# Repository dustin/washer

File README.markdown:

This is the code that supports my [laundry][blog] project.

[blog]: http://dustin.sallings.org/2012/09/16/wash.html

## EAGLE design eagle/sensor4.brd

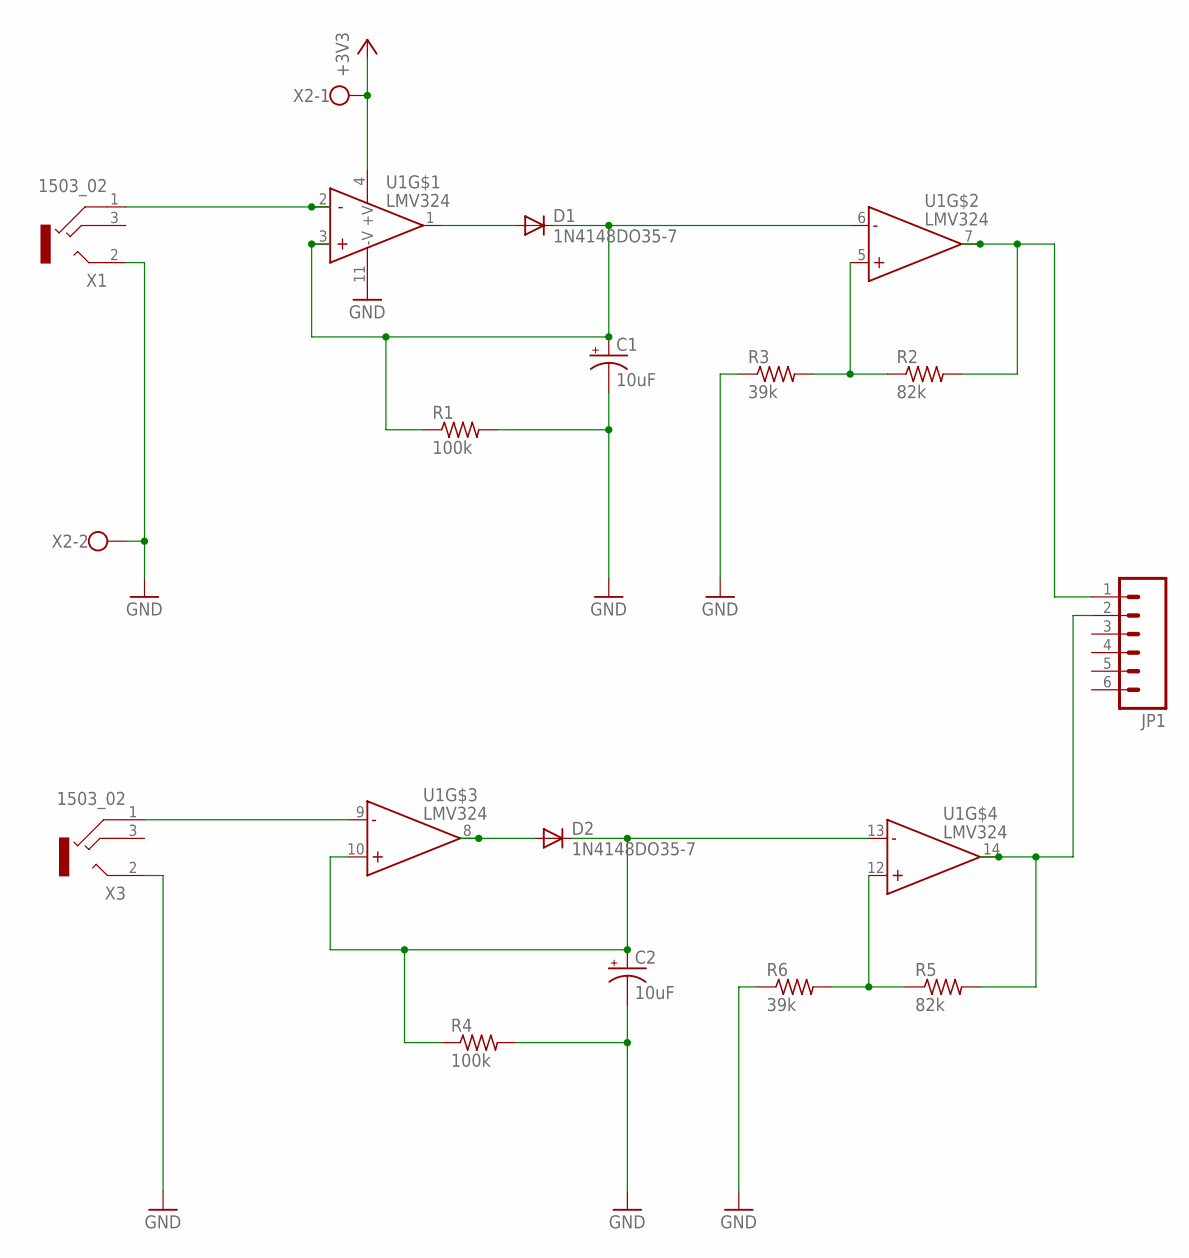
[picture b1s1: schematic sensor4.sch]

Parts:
C1, C2: 10uF; E2,5-5
D1, D2: 1N4148DO35-7; DO35-7
JP1: M06SIP; 1X06
R1, R4: 100k; 0207/10
R2, R5: 82k; 0207/10
R3, R6: 39k; 0207/10
U1: LMV324; SO014
X1, X3: 1503_02
X2: W237-102

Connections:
+3V3: U1.4 (+V), X2.1
GND: C1.-, C2.-, R1.2, R3.1, R4.2, R6.1, U1.11 (-V), X1.2, X2.2, X3.2
unnamed: D1.A, U1.1 (OUT)
unnamed: C1.+, D1.C, R1.1, U1.3 (+IN), U1.6 (-IN)
unnamed: D2.A, U1.8 (OUT)
unnamed: C2.+, D2.C, R4.1, U1.10 (+IN), U1.13 (-IN)
unnamed: R2.1, R3.2, U1.5 (+IN)
unnamed: U1.2 (-IN), X1.1
unnamed: JP1.1, R2.2, U1.7 (OUT)
unnamed: R5.1, R6.2, U1.12 (+IN)
unnamed: U1.9 (-IN), X3.1
unnamed: JP1.2, R5.2, U1.14 (OUT)

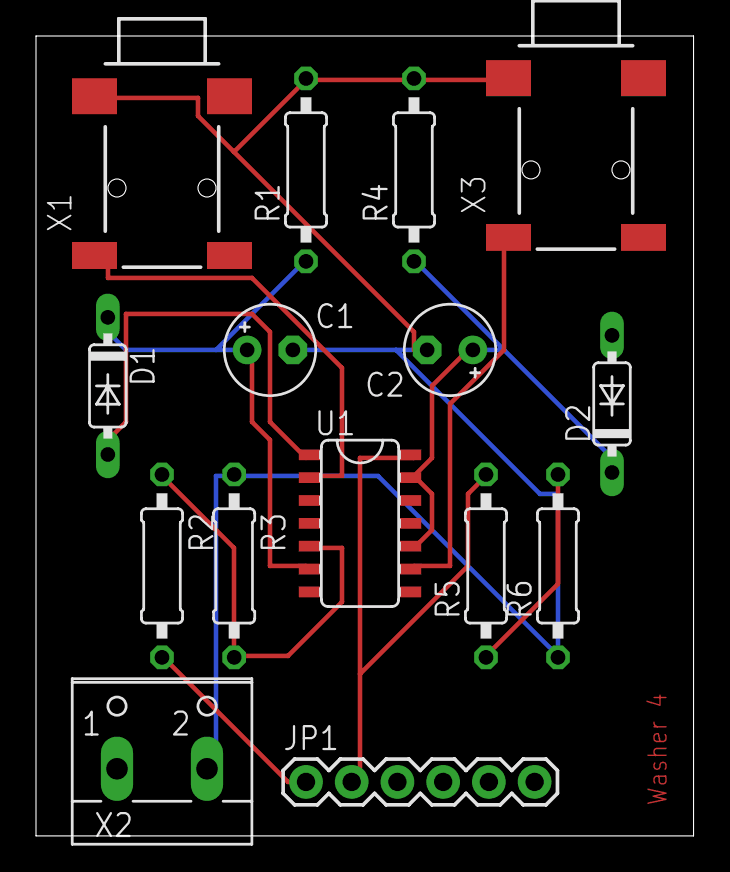
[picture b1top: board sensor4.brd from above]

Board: 2 copper layers, 36.5 x 44.4 mm, 15 parts (0 on the bottom side), 12 nets.

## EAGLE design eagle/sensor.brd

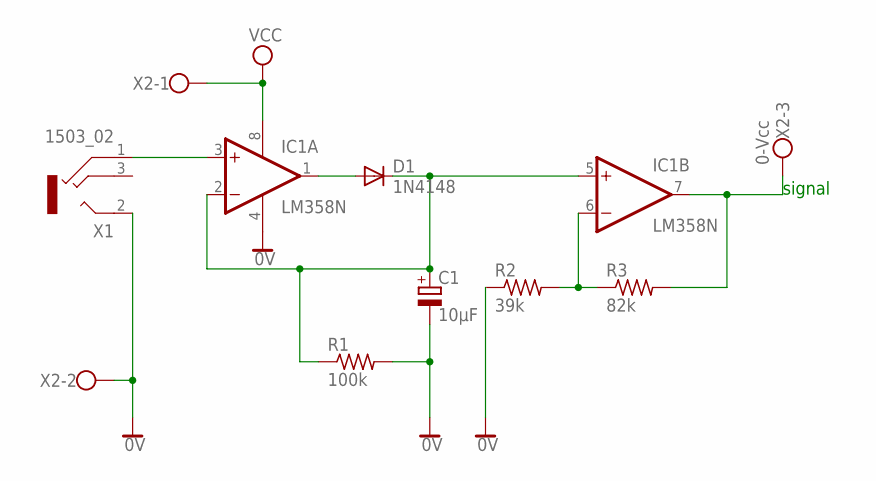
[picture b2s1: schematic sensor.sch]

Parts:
C1: 10µF; E2,5-6E
D1: 1N4148; DO35-10
IC1: LM358N; DIL08
R1: 100k; 0207/10
R2: 39k; 0207/10
R3: 82k; 0207/10
X1: 1503_02
X2: 0-Vcc; W237-103

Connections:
0V: C1.-, IC1.4 (V-), R1.2, R2.1, X1.2, X2.2
unnamed: C1.+, D1.C, IC1.2 (-IN), IC1.5 (+IN), R1.1
unnamed: IC1.6 (-IN), R2.2, R3.1
unnamed: D1.A, IC1.1 (OUT)
unnamed: IC1.7 (OUT), R3.2, X2.3
unnamed: IC1.3 (+IN), X1.1
VCC: IC1.8 (V+), X2.1

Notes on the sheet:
signal

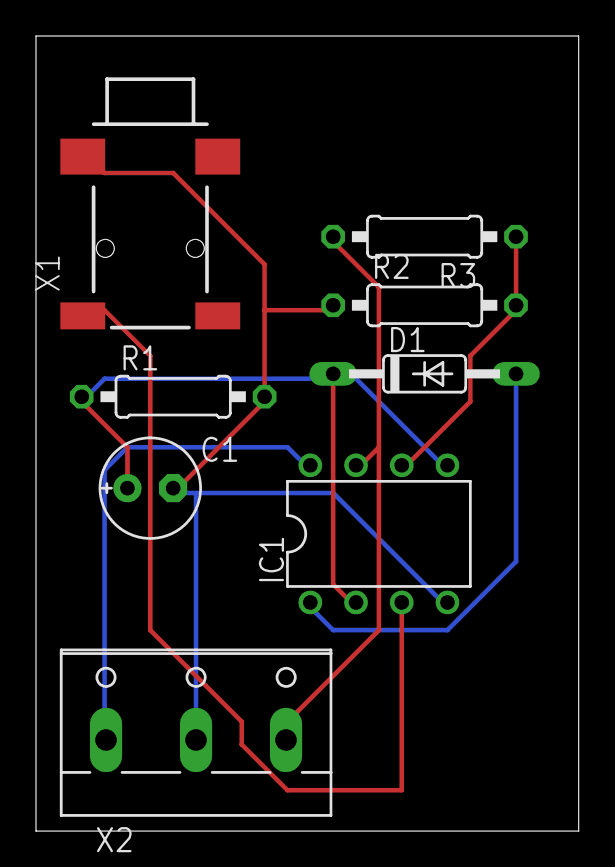
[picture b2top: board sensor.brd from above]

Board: 2 copper layers, 30.1 x 44.2 mm, 8 parts (0 on the bottom side), 7 nets.

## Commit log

2011-12-25 Semi-working version tested in garage.
2011-12-26 Report time since last state change.
2011-12-26 Conveniently clean date formatting.
2011-12-26 Indicate state on/off
2011-12-26 Newer lighter home protocol.
2011-12-26 Removed an unused var.
2011-12-26 More protocol updates.
2011-12-26 Added a go based monitor prog.
2011-12-26 Include previous time in event state change.
2011-12-26 gofmt -- I should automate this at some point.
2011-12-26 Build and initialize the struct.
2011-12-27 Keep transmitting the high since last ACK.
2011-12-27 Static'd out the variables.
2011-12-27 Track maximum value seen since ACK.
2012-01-02 Minor refactoring.
2012-01-02 Added support for mocking a device.
2012-01-02 Added a simple web interface.
2012-01-09 Slipping in a blinking state between off/on cycle.
2012-01-09 Replace serial delays with flushes.
2012-01-09 Clean up blink state overlay.
2012-02-08 Updated for 'go build'
2012-06-22 Ignore the built monitor.
2012-06-22 RS232 API updates.
2012-06-23 Deal with empty lines from the monitor.
2012-06-23 Use custom marshaler.
2012-06-23 Don't be confusing and alias my types.
2012-06-23 Notification with a stability timer.
2012-06-23 Allow user to specify which events receive the notification.
2012-06-23 Have to actually start the notifier.
2012-06-24 Added HTML view.
    Since rendering the JSON on my phone was awful.
2012-06-24 Set CORS and content type headers for JSON.
2012-06-25 Building and deploying Arduino code on Linux now.
2012-10-20 Log to syslog.
2012-10-20 Don't duplicate the timestamps when logging to syslog.
2012-11-05 Fix notification disabling.
2013-07-29 Renamed nma
2013-07-29 Renamed rs232
2013-08-04 nma priority level update
2013-09-14 Initialize globals outside of init
2013-09-14 No need to name the tracker's state type
2013-09-15 Added a README
2013-09-16 Original eagle work.
2013-09-16 Rerouted board for two layer print.
2013-09-16 reduce board size
2013-09-22 Added preliminary dual sensor design
2013-09-22 Reshaped the board slightly more sensibly
2013-09-22 Switch to separate header pin set for signal
2013-09-23 Replace two LM358s with one LMV324

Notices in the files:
parts and their libraries:
SparkFun-Connectors: Licensing: CC v3.0 Share-Alike You are welcome to use this library for commercial purposes.
